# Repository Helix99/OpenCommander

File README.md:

# OpenCommander
USB Fan and temprature sensor managment firmware, application and board.

I have a linux server but the supermicro motherboard has limited fan headders and thermal zones. I wanted a much more flexible thermal management solution for it. 

Can manage 6 groups of 2 fans (12 total)
Up to 5 x DS18B20 temprature sensors
Posibillity to disable fan 5 and use pin as input from motherboard fan headder (yet to be implimented in firmware)

Emulates the corsair commander pro firmware so that the fans and tempratures show up in Linux using the in tree corsair module.

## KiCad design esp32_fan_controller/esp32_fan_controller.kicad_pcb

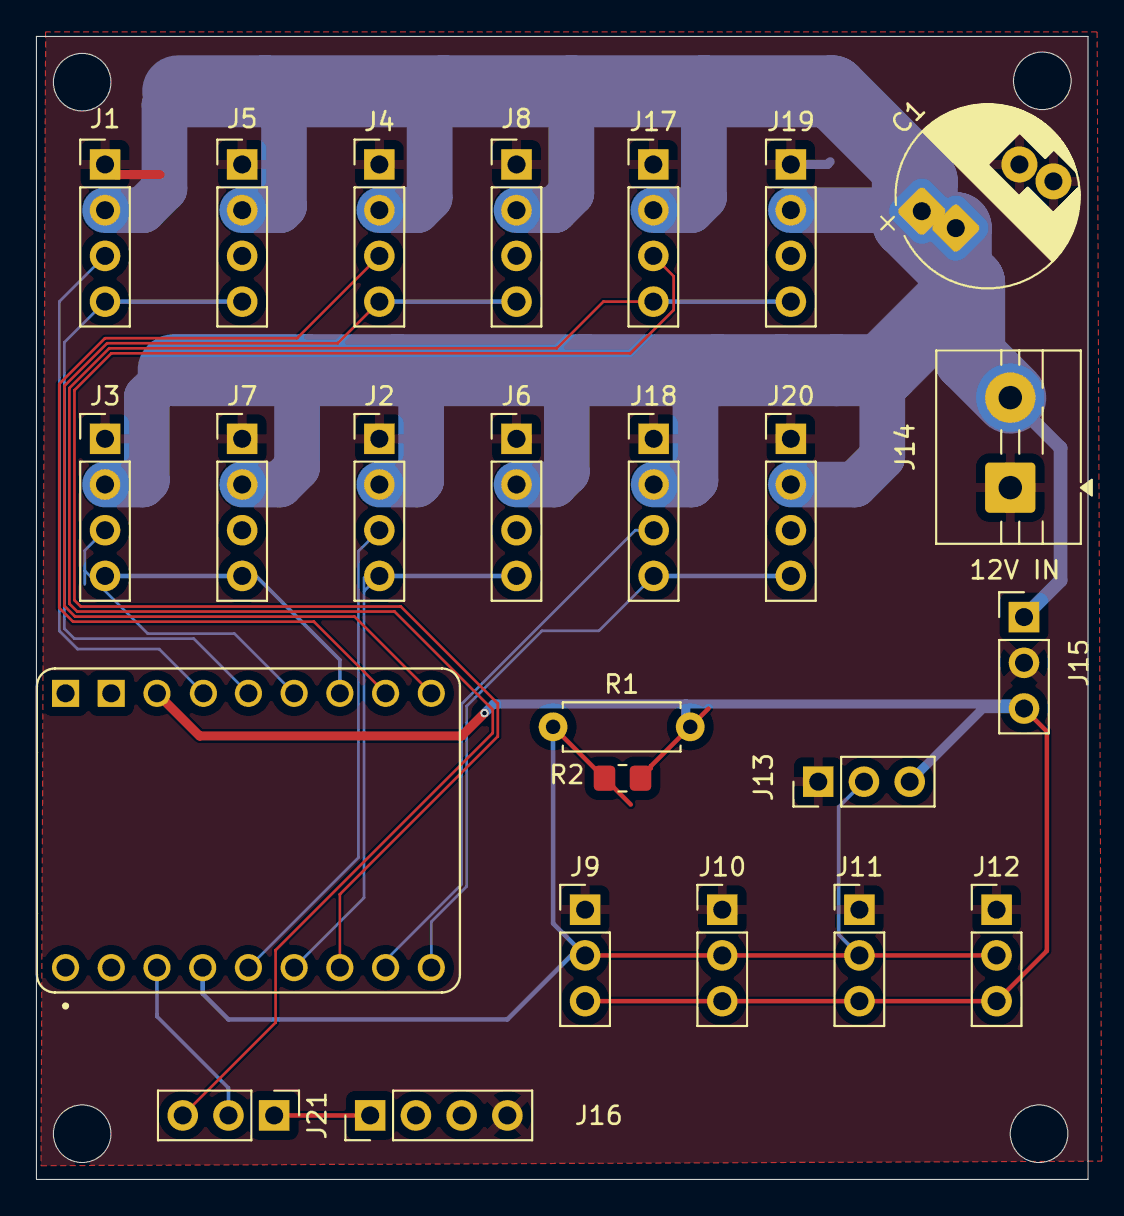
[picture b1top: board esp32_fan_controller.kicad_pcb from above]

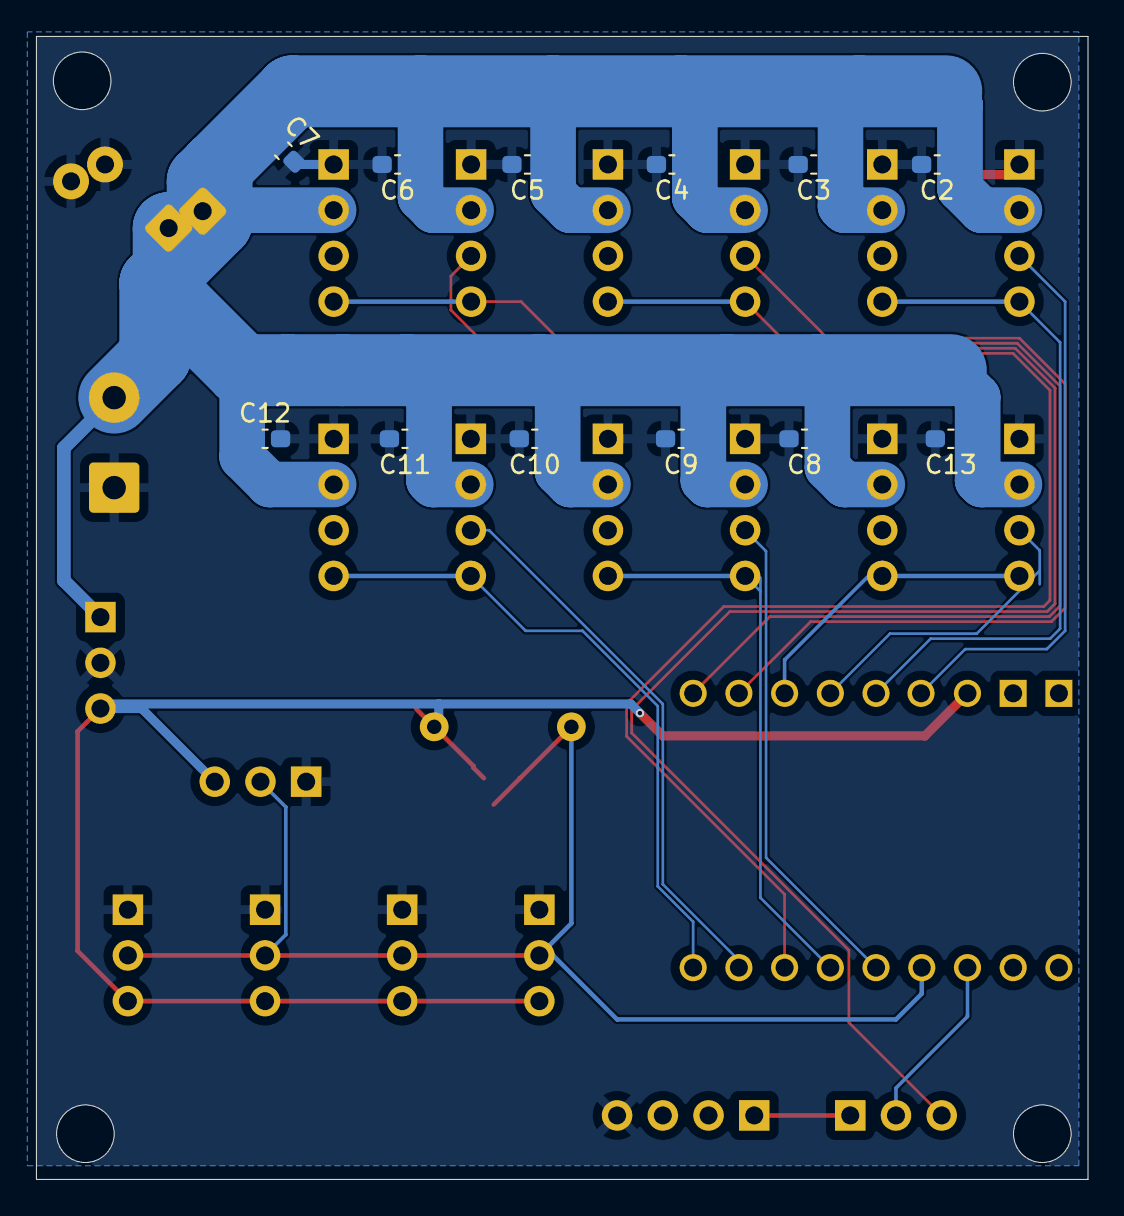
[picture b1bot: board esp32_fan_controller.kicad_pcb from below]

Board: 2 copper layers, 58.4 x 63.5 mm, 37 parts (12 on the bottom side), 18 nets.

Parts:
C1: C_Polarized; CP_Radial_D10.0mm_P5.00mm_P7.50mm
C2, C3, C4, C5, C6, C7, C8, C9, C10, C11, C12, C13: C; C_0603_1608Metric_Pad1.08x0.95mm_HandSolder
J1: FAN 1A; PinHeader_1x04_P2.54mm_Vertical
J2: FAN 2A; PinHeader_1x04_P2.54mm_Vertical
J3: FAN 3A; PinHeader_1x04_P2.54mm_Vertical
J4: FAN 4A; PinHeader_1x04_P2.54mm_Vertical
J5: FAN 1B; PinHeader_1x04_P2.54mm_Vertical
J6: FAN2B; PinHeader_1x04_P2.54mm_Vertical
J7: FAN 3B; PinHeader_1x04_P2.54mm_Vertical
J8: FAN 4B; PinHeader_1x04_P2.54mm_Vertical
J9: TEMP2; PinHeader_1x03_P2.54mm_Vertical
J10: TEMP1; PinHeader_1x03_P2.54mm_Vertical
J11: TEMP3; PinHeader_1x03_P2.54mm_Vertical
J12: TEMP4; PinHeader_1x03_P2.54mm_Vertical
J13: TEMP5; PinHeader_1x03_P2.54mm_Vertical
J14: 12V IN; TerminalBlock_MaiXu_MX126-5.0-02P_1x02_P5.00mm
J15: POWER REG; PinHeader_1x03_P2.54mm_Vertical
J16: MOBO FAN; PinHeader_1x04_P2.54mm_Vertical
J17: FAN 5A; PinHeader_1x04_P2.54mm_Vertical
J18: FAN 6A; PinHeader_1x04_P2.54mm_Vertical
J19: FAN 5B; PinHeader_1x04_P2.54mm_Vertical
J20: FAN 6B; PinHeader_1x04_P2.54mm_Vertical
J21: GPIO1; PinHeader_1x03_P2.54mm_Vertical
R1: R; R_Axial_DIN0207_L6.3mm_D2.5mm_P7.62mm_Horizontal
R2: 4.7R; R_0805_2012Metric_Pad1.20x1.40mm_HandSolder
U1: ESP32-S3 SuperMini; ESP32-S3-SuperMini

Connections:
+3.3V: J9.3, J10.3, J11.3, J12.3, J13.3, J15.3, R1.2, R2.2
+12V: C1.1, C2.1, C3.1, C4.1, C5.1, C6.1, C7.1, C8.1, C9.1, C10.1, C11.1, C12.1, C13.1, J1.2, J2.2, J3.2, J4.2, J5.2, J6.2, J7.2, J8.2, J14.2, J15.1, J17.2, J18.2, J19.2, J20.2
GND: C1.2, C2.2, C3.2, C4.2, C5.2, C6.2, C7.2, C8.2, C9.2, C10.2, C11.2, C12.2, C13.2, J1.1, J2.1, J3.1, J4.1, J5.1, J6.1, J7.1, J8.1, J9.1, J10.1, J11.1, J12.1, J13.1, J14.1, J15.2, J16.4, J17.1, J18.1, J19.1, J20.1
unnamed: J1.3, U1.13 (GPIO13)
unnamed: J1.4, J5.4, U1.12 (GPIO12)
unnamed: J2.3, U1.3 (GPIO3)
unnamed: J2.4, J6.4, U1.4 (GPIO4)
unnamed: J3.3, U1.11 (GPIO11)
unnamed: J3.4, J7.4, U1.10 (GPIO10)
unnamed: J4.3, U1.9 (GPIO9)
unnamed: J4.4, J8.4, U1.8 (GPIO8)
unnamed: J9.2, J10.2, J11.2, J12.2, J13.2, R1.1, R2.1, U1.2 (GPI02)
unnamed: J16.1, J21.1
unnamed: J17.3, U1.5 (GPIO5)
unnamed: J17.4, J19.4, J21.3
unnamed: J18.3, U1.6 (GPIO6)
unnamed: J18.4, J20.4, U1.7 (GPIO7)
unnamed: J21.2, U1.1 (GPIO1)

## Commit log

2026-02-21 image
2026-02-21 Update README with project details and features
    Added project description and features to README.
2026-02-21 Update README to reflect 6 PWM fans support
2026-02-21 Update README with project details and capabilities
    Expanded project description and clarified fan and sensor management capabilities.
